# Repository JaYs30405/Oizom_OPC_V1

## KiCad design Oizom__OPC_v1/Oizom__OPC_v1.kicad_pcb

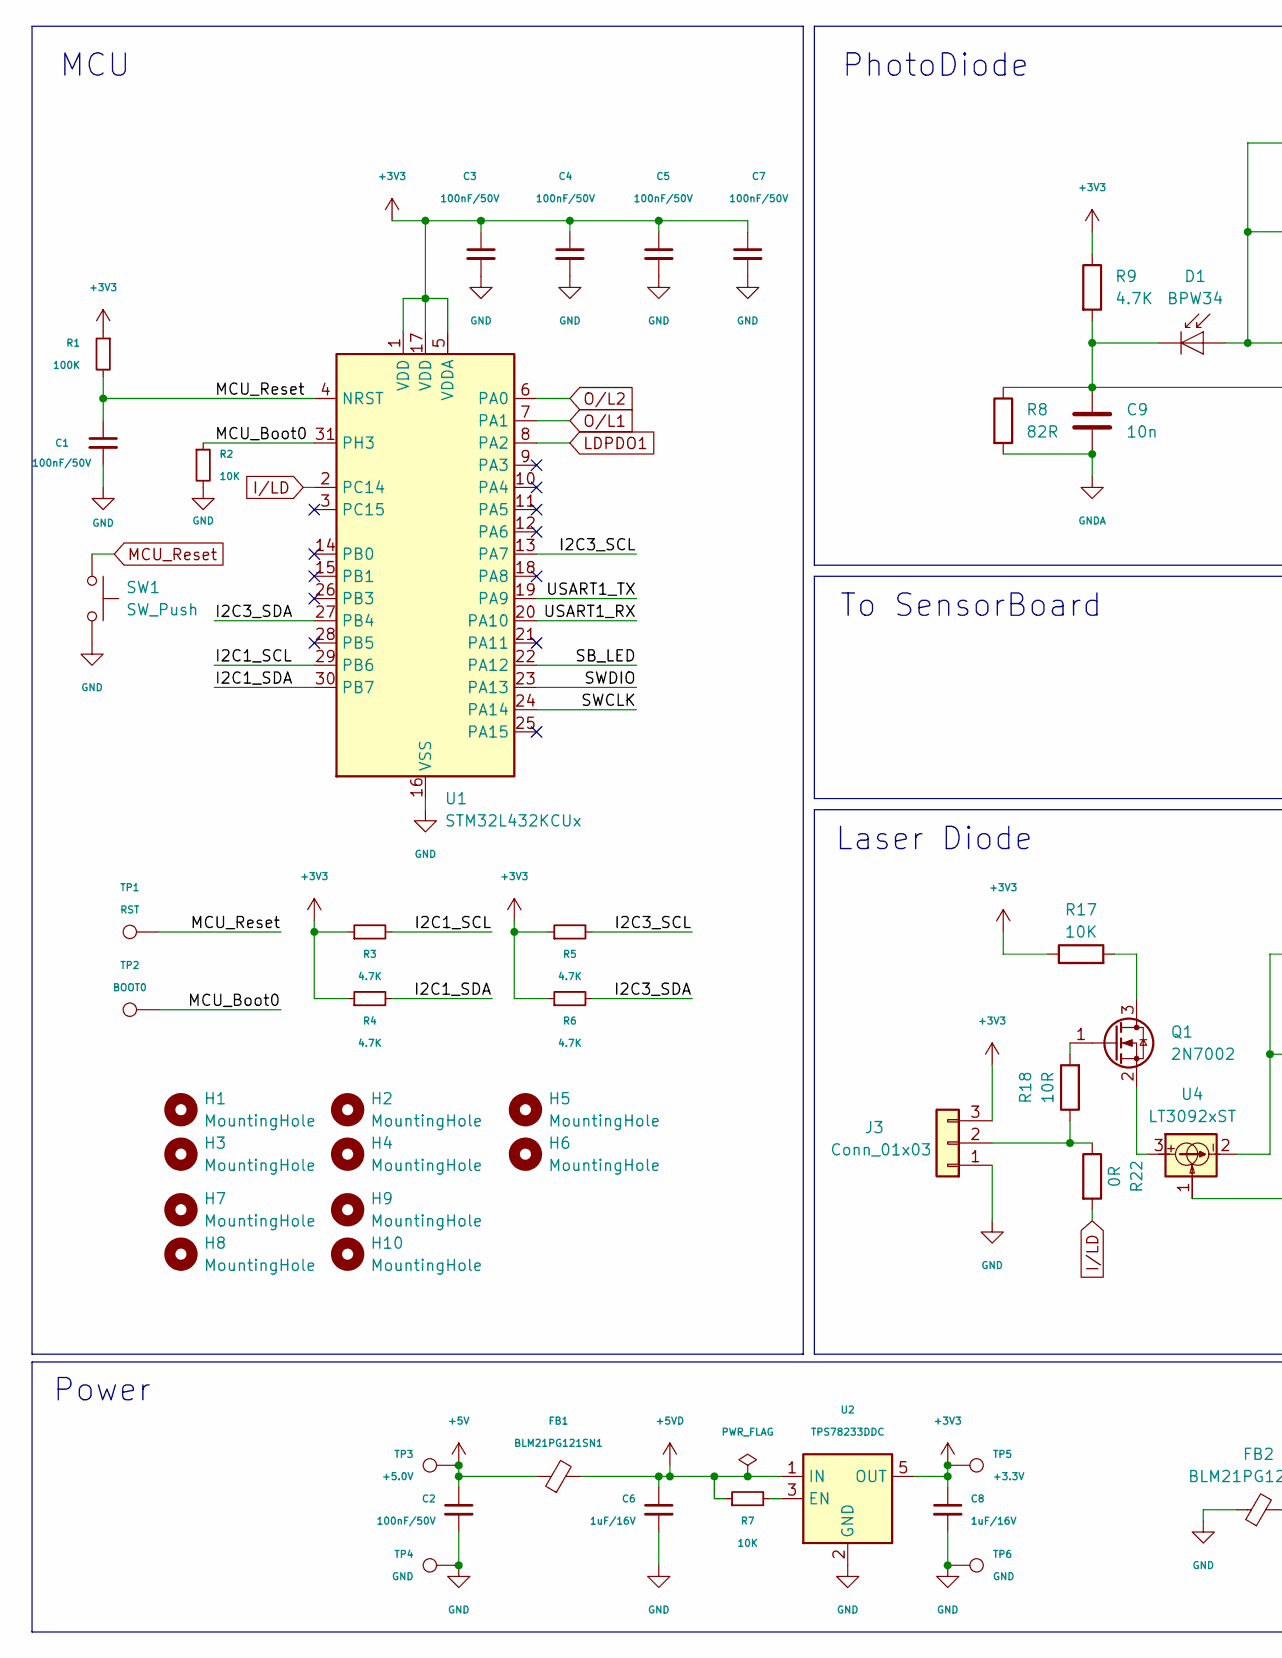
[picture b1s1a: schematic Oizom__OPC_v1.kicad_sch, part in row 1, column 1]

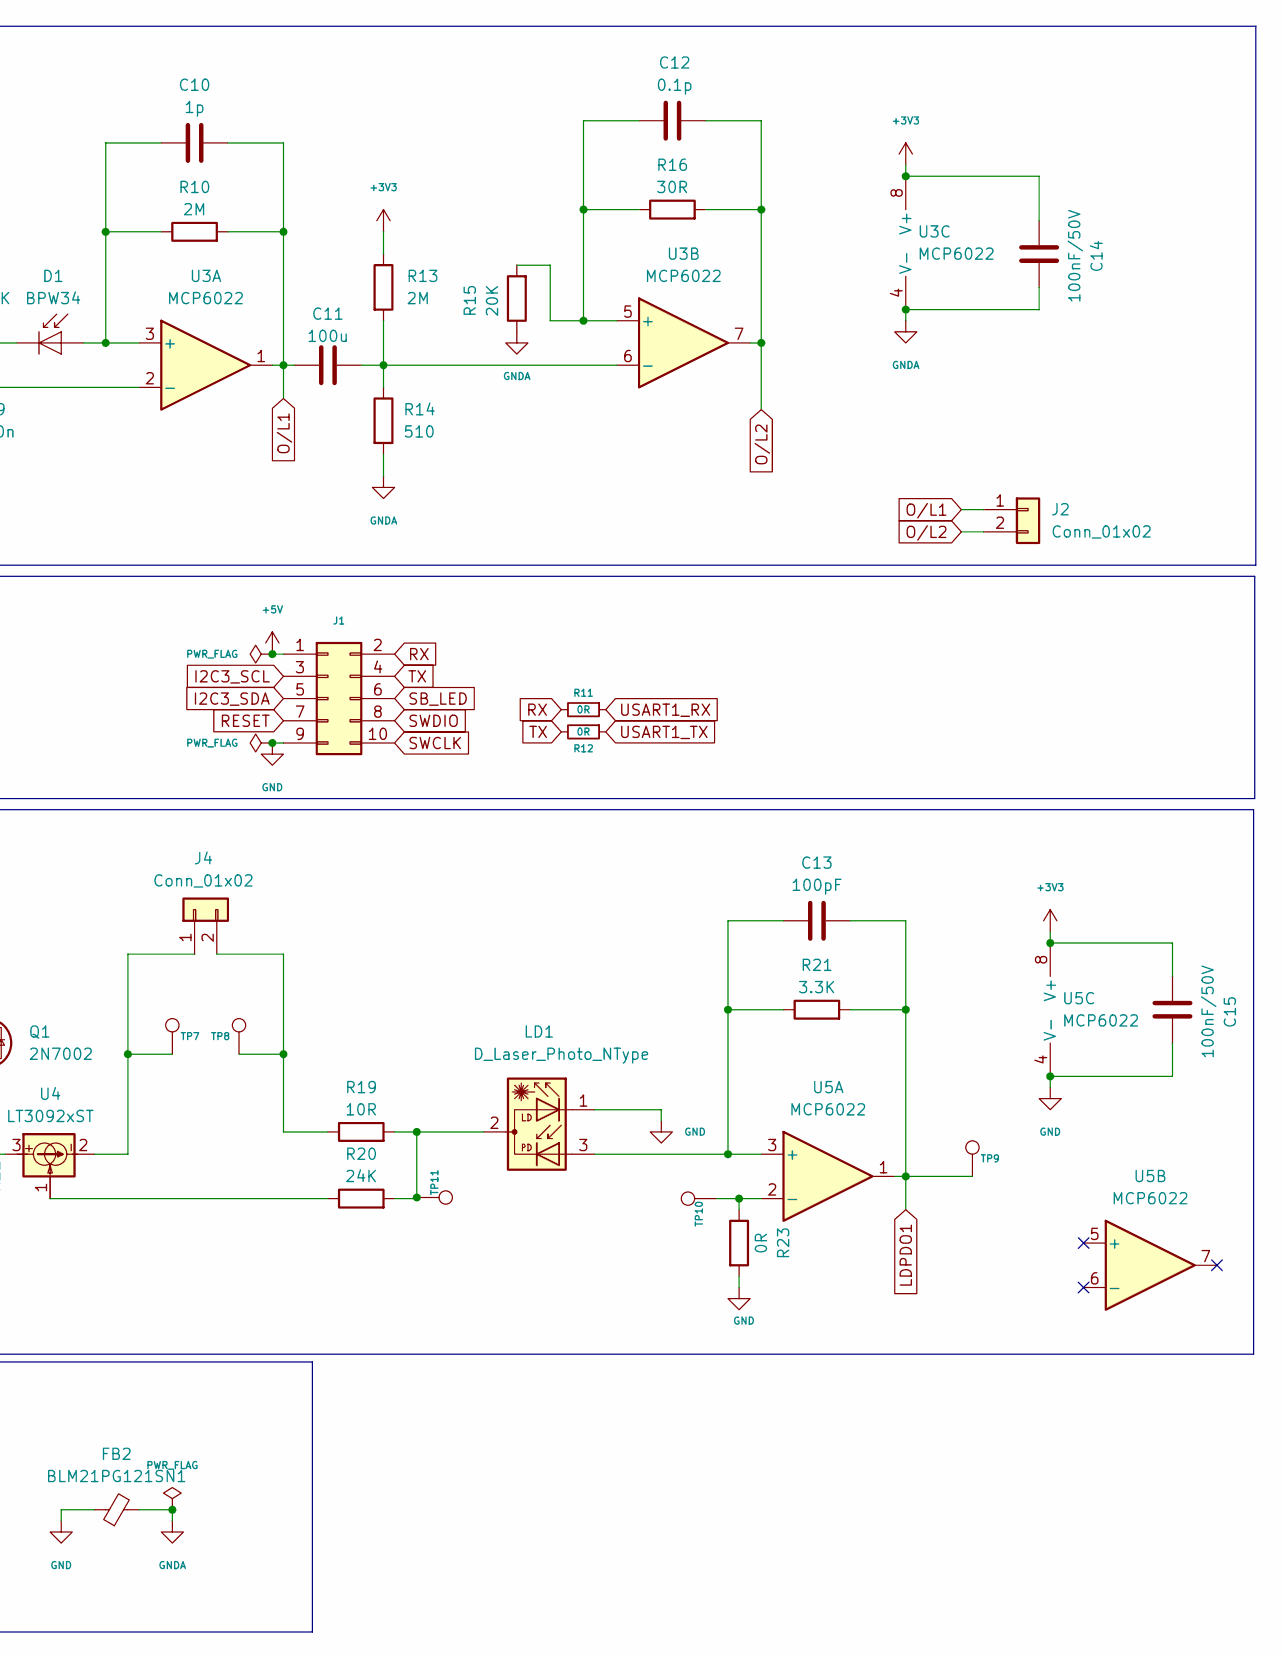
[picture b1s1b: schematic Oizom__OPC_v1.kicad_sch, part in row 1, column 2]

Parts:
C1, C2, C3, C4, C5, C7, C14, C15: 100nF/50V; C_0603_1608Metric
C6, C8: 1uF/16V; C_0603_1608Metric
C9: 10n; C_0603_1608Metric
C10: 1p; C_0603_1608Metric
C11: 100u; C_1210_3225Metric_Pad1.33x2.70mm_HandSolder
C12: 0.1p; C_0603_1608Metric
C13: 100pF; C_0603_1608Metric
D1: BPW34; Osram_DIL2_4.3x4.65mm_P5.08mm
FB1, FB2: BLM21PG121SN1; L_0805_2012Metric
H1, H2, H3, H4, H5, H6, H7, H8, H9, H10: MountingHole; MountingHole_4mm
J1: Conn_02x05_Odd_Even; IDC-Header_2x05_P2.54mm_Vertical
J2, J4: Conn_01x02; PinHeader_1x02_P2.54mm_Vertical
J3: Conn_01x03; PinHeader_1x03_P2.54mm_Vertical
LD1: D_Laser_Photo_NType; FanPinHeader_1x03_P2.54mm_Vertical
Q1: 2N7002; SOT-23
R1: 100K; R_0603_1608Metric
R2, R7, R17: 10K; R_0603_1608Metric
R3, R4, R5, R6, R9: 4.7K; R_0603_1608Metric
R8: 82R; R_0603_1608Metric
R10: 2M; R_0603_1608Metric_Pad0.98x0.95mm_HandSolder
R11, R12, R22, R23: 0R; R_0603_1608Metric
R13: 2M; R_0603_1608Metric
R14: 510; R_0603_1608Metric
R15: 20K; R_0603_1608Metric
R16: 30R; R_0603_1608Metric_Pad0.98x0.95mm_HandSolder
R18, R19: 10R; R_0603_1608Metric
R20: 24K; R_0603_1608Metric
R21: 3.3K; R_0603_1608Metric_Pad0.98x0.95mm_HandSolder
SW1: SW_Push; SW_Push_1P1T_NO_CK_KMR2
TP1, TP7, TP8, TP9, TP10, TP11: RST; TestPoint_Pad_D1.0mm
TP2: BOOT0; TestPoint_Pad_D1.0mm
TP3: +5.0V; TestPoint_Pad_D1.0mm
TP4, TP6: GND; TestPoint_Pad_D1.0mm
TP5: +3.3V; TestPoint_Pad_D1.0mm
U1: STM32L432KCUx; QFN-32-1EP_5x5mm_P0.5mm_EP3.45x3.45mm
U2: TPS78233DDC; SOT-23-5
U3, U5: MCP6022; SOIC-8_3.9x4.9mm_P1.27mm
U4: LT3092xST; SOT-223-3_TabPin2

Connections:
+3V3: C3.1, C4.1, C5.1, C7.1, C8.1, C14.1, C15.1, J3.3, R1.1, R3.1, R4.1, R5.1, R6.1, R9.1, R13.1, R17.1, TP5.1 (1_1), U1.1 (VDD), U1.5 (VDDA), U1.17 (VDD), U2.5 (OUT), U3.8 (V+), U5.8 (V+)
+5V: C2.1, FB1.1, J1.1, TP3.1 (1_1)
+5VD: C6.1, FB1.2, R7.1, U2.1 (IN)
/I2C1_SCL: R3.2, U1.29 (PB6)
/I2C1_SDA: R4.2, U1.30 (PB7)
/MCU_Boot0: R2.1, TP2.1 (1_1), U1.31 (PH3)
GND: C1.2, C2.2, C3.2, C4.2, C5.2, C6.2, C7.2, C8.2, C15.2, FB2.1, J1.9, J3.1, LD1.1, R2.2, R23.2, SW1.2, TP4.1 (1_1), TP6.1 (1_1), U1.16 (VSS), U1.32 (VSS), U1.33 (VSS), U2.2 (GND), U2.4 (GND), U5.4 (V-)
GNDA: C9.2, C14.2, FB2.2, R8.2, R14.2, R15.1, U3.4 (V-)
I2C3_SCL: J1.3, R5.2, U1.13 (PA7)
I2C3_SDA: J1.5, R6.2, U1.27 (PB4)
I/LD: R22.2, U1.2 (PC14)
LDPDO1: C13.2, R21.2, TP9.1 (1_1), U1.8 (PA2), U5.1
MCU_Reset: C1.1, R1.2, SW1.1, TP1.1 (1_1), U1.4 (NRST)
unnamed: C10.1, D1.2 (A), R10.1, U3.3 (+)
unnamed: C9.1, D1.1 (K), R8.1, R9.2, U3.2 (-)
unnamed: J3.2, R18.1, R22.1
unnamed: J4.1, TP7.1 (1_1), U4.2
unnamed: J4.2, R19.1, TP8.1 (1_1)
unnamed: LD1.2, R19.2, R20.2, TP11.1 (1_1)
unnamed: Q1.3 (D), R17.2
unnamed: Q1.1 (G), R18.2
unnamed: Q1.2 (S), U4.3
unnamed: R20.1, U4.1
unnamed: R7.2, U2.3 (EN)
unnamed: C12.1, R15.2, R16.1, U3.5 (+)
unnamed: C11.2, R13.2, R14.1, U3.6 (-)
unnamed: C13.1, LD1.3, R21.1, U5.3 (+)
unnamed: R23.1, TP10.1 (1_1), U5.2 (-)
O/L1: C10.2, C11.1, J2.1, R10.2, U1.7 (PA1), U3.1
O/L2: C12.2, J2.2, R16.2, U1.6 (PA0), U3.7
RESET: J1.7
RX: J1.2, R11.2
SB_LED: J1.6, U1.22 (PA12)
SWCLK: J1.10, U1.24 (PA14)
SWDIO: J1.8, U1.23 (PA13)
TX: J1.4, R12.2
USART1_RX: R11.1, U1.20 (PA10)
USART1_TX: R12.1, U1.19 (PA9)

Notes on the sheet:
To SensorBoard
PhotoDiode
Power
MCU
Laser Diode

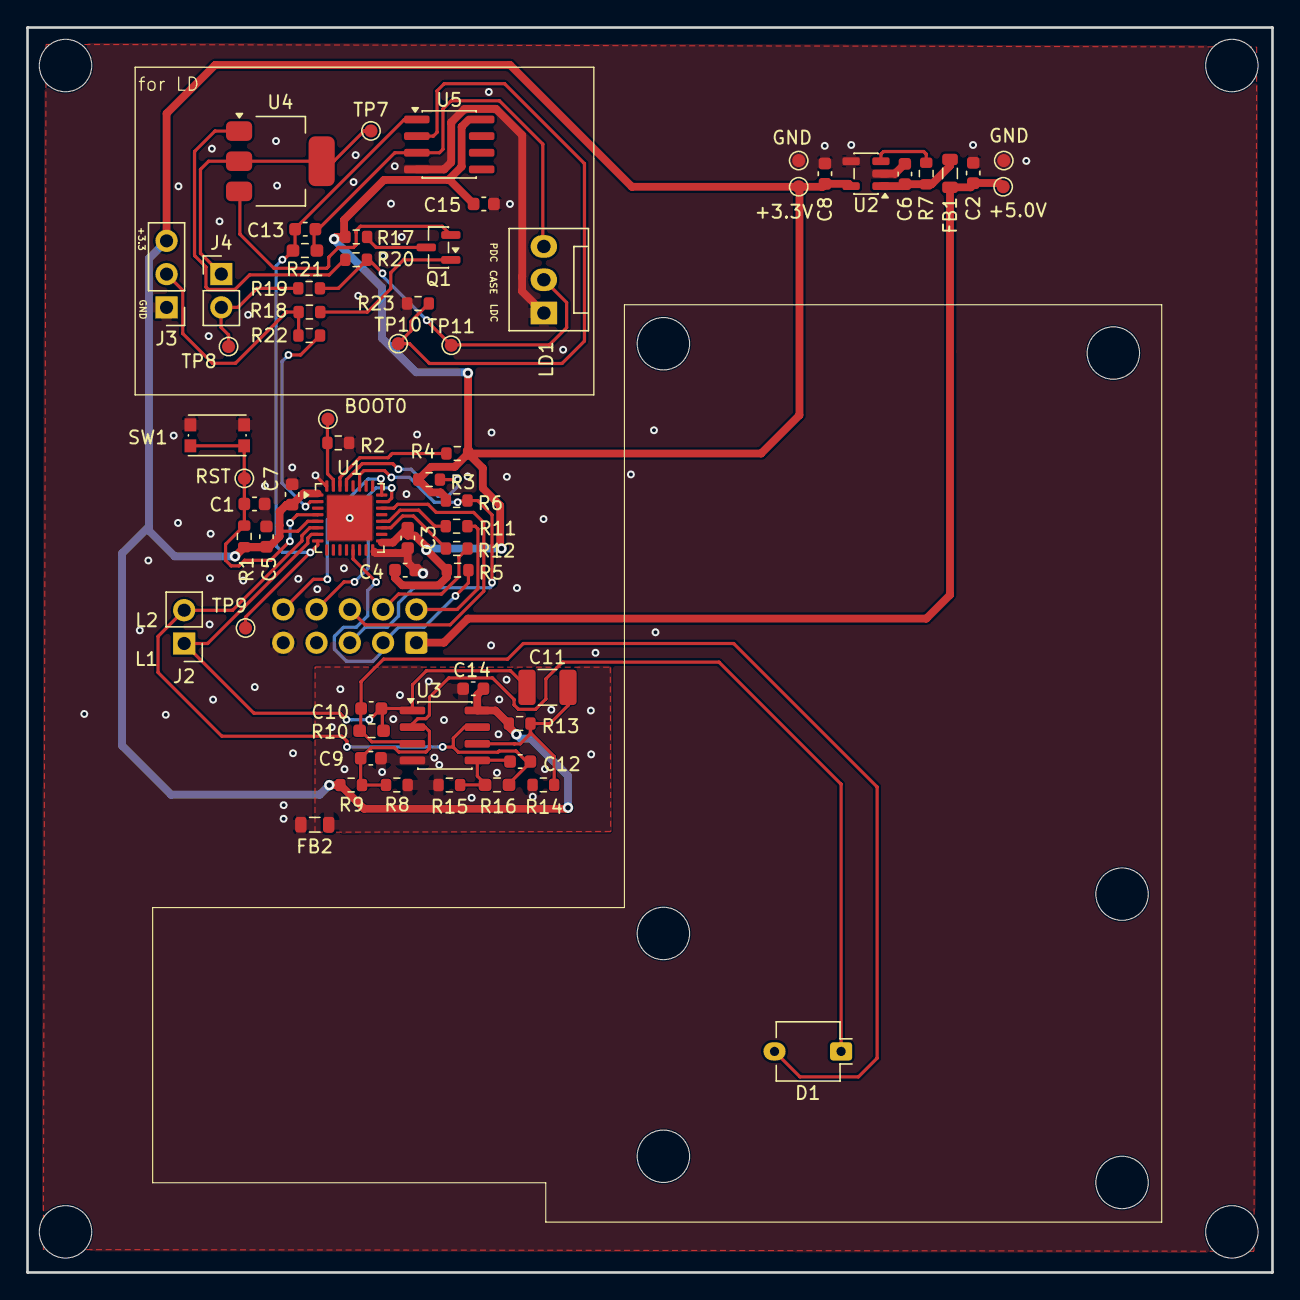
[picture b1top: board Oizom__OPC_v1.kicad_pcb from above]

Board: 2 copper layers, 95.0 x 95.0 mm, 74 parts (1 on the bottom side), 37 nets.

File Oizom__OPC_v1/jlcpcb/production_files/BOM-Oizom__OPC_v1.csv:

Comment,Designator,Footprint,LCSC,Quantity
0.1p,C12,C_0603_1608Metric,C304680,1
0R,"R11,R12,R22,R23",R_0603_1608Metric,C21189,4
100K,R1,R_0603_1608Metric,C25803,1
100nF/50V,"C1,C14,C15,C2,C3,C4,C5,C7",C_0603_1608Metric,C14663,8
100pF,C13,C_0603_1608Metric,C14858,1
100u,C11,C_1210_3225Metric_Pad1.33x2.70mm_HandSolder,C23742,1
10K,"R17,R2,R7",R_0603_1608Metric,C25804,3
10R,"R18,R19",R_0603_1608Metric,C22859,2
10n,C9,C_0603_1608Metric,C57112,1
1p,C10,C_0603_1608Metric,C37117,1
1uF/16V,"C6,C8",C_0603_1608Metric,C15849,2
20K,R15,R_0603_1608Metric,C4184,1
24K,R20,R_0603_1608Metric,C23352,1
2M,"R10,R13",R_0603_1608Metric_Pad0.98x0.95mm_HandSolder,C22976,2
2N7002,Q1,SOT-23,C8545,1
3.3K,R21,R_0603_1608Metric_Pad0.98x0.95mm_HandSolder,C22978,1
30R,R16,R_0603_1608Metric_Pad0.98x0.95mm_HandSolder,C22985,1
4.7K,"R3,R4,R5,R6,R9",R_0603_1608Metric,C23162,5
510,R14,R_0603_1608Metric,C23193,1
82R,R8,R_0603_1608Metric,C25260,1
BLM21PG121SN1,"FB1,FB2",L_0805_2012Metric,C79382,2
LT3092xST,U4,SOT-223-3_TabPin2,C117207,1
MCP6022,"U3,U5",SOIC-8_3.9x4.9mm_P1.27mm,C57639,2
STM32L432KCUx,U1,QFN-32-1EP_5x5mm_P0.5mm_EP3.45x3.45mm,C1337280,1
SW_Push,SW1,SW_Push_1P1T_NO_CK_KMR2,C221675,1
TPS78233DDC,U2,SOT-23-5,C14878,1
